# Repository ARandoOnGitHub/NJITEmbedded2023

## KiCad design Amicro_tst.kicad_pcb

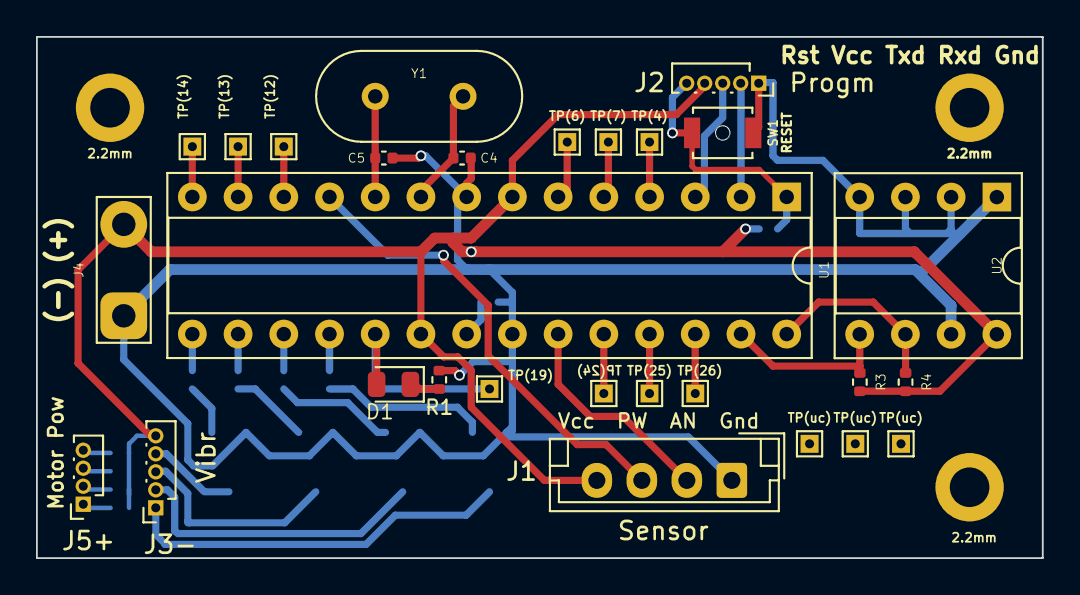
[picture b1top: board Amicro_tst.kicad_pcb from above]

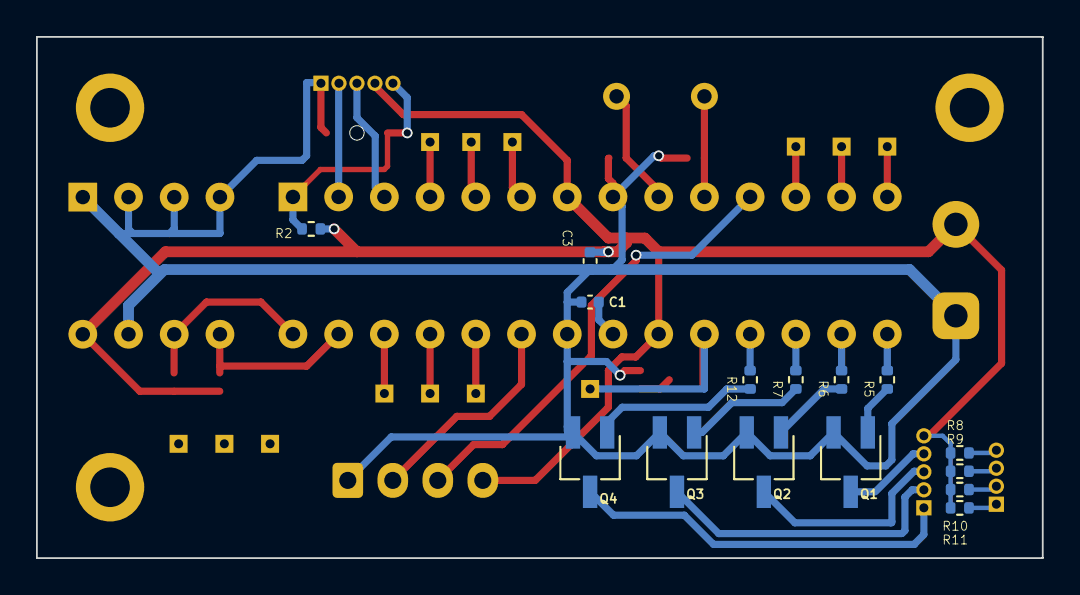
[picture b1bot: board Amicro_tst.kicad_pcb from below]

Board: 2 copper layers, 55.9 x 29.0 mm, 46 parts (15 on the bottom side), 39 nets.

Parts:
2.2mm, 2.2mm#2, 2.2mm#3: 2.2; MountingHole_2.2mm_M2_DIN965_Pad
C1, C3: .1uf; C_0402_1005Metric
C4, C5: 22pf; C_0402_1005Metric
D1: LED; LED_0805_2012Metric
J1: Sensor; JST_EH_B4B-EH-A_1x04_P2.50mm_Vertical
J2: Progm; PinSocket_1x05_P1.00mm_Vertical
J3-: Vibr; PinSocket_1x05_P1.00mm_Vertical
J4: Pow; TestPoint_2Pads_Pitch5.08mm_Drill1.3mm
J5+: Motor Pow; PinSocket_1x04_P1.00mm_Vertical
Q1, Q2, Q3, Q4: Q_NPN_BEC; SC-59_Handsoldering
R1, R5, R6, R7, R12: 1k; R_0402_1005Metric
R2: 10k; R_0402_1005Metric
R3, R4: 4.7k; R_0402_1005Metric
R8, R9, R10, R11: 33; R_0402_1005Metric
SW1: RESET; SW_SPST_B3U-1000P-B
TP(4), TP(6), TP(7), TP(12), TP(13), TP(14), TP(19), TP(24), TP(25), TP(26): TP; TestPoint_THTPad_1.0x1.0mm_Drill0.5mm
TP(uc): TP; TestPoint_THTPad_1.0x1.0mm_Drill0.5mm
TP(uc)#2, TP(uc)#3: TP; TestPoint_THTPad_1.0x1.0mm_Drill0.5mm
U1: ATmega328-P; DIP-28_W7.62mm_Socket
U2: 24LC512; DIP-8_W7.62mm_Socket
Y1: Crystal; Crystal_HC49-4H_Vertical

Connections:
AN: J1.2, U1.23 (PC0)
GND: C1.2, C3.2, C4.2, C5.2, J1.1, J2.1, J4.1, Q1.2 (E), Q2.2 (E), Q3.2 (E), Q4.2 (E), R1.1, SW1.2, U1.8 (GND), U1.22 (GND), U2.1 (A0), U2.2 (A1), U2.3 (A2), U2.4 (GND), U2.7 (WP)
M0: J3-.4, Q1.3 (C)
M1: J3-.3, Q2.3 (C)
M2: J3-.2, Q3.3 (C)
M3: J3-.1, Q4.3 (C)
Mt0+: J5+.4, R8.1
Mt1+: J5+.3, R9.1
Mt2+: J5+.2, R10.1
Mt3+: J5+.1, R11.1
unnamed: C1.1, U1.21 (AREF)
unnamed: C4.1, U1.9 (XTAL1/PB6), Y1.2
unnamed: C5.1, U1.10 (XTAL2/PB7), Y1.1
unnamed: D1.1 (K), R1.2
unnamed: D1.2 (A), TP(19).1, U1.19 (PB5)
unnamed: Q1.1 (B), R5.2
unnamed: Q2.1 (B), R6.2
unnamed: Q3.1 (B), R7.2
unnamed: Q4.1 (B), R12.2
unnamed: TP(4).1, U1.4 (PD2)
unnamed: TP(6).1, U1.6 (PD4)
unnamed: TP(7).1, U1.5 (PD3)
unnamed: TP(12).1, U1.12 (PD6)
unnamed: TP(13).1, U1.13 (PD7)
unnamed: TP(14).1, U1.14 (PB0)
unnamed: TP(24).1, U1.24 (PC1)
unnamed: TP(25).1, U1.25 (PC2)
unnamed: TP(26).1, U1.26 (PC3)
PW: J1.3, U1.11 (PD5)
PWM0: R5.1, U1.15 (PB1)
PWM1: R6.1, U1.16 (PB2)
PWM2: R7.1, U1.17 (PB3)
PWM3: R12.1, U1.18 (PB4)
RESET: J2.5, R2.2, SW1.1, U1.1 (~RESET/PC6)
RXD: J2.2, U1.2 (PD0)
SCL: R4.1, U1.28 (PC5), U2.6 (SCL)
SDA: R3.1, U1.27 (PC4), U2.5 (SDA)
TXD: J2.3, U1.3 (PD1)
VCC: C3.1, J1.4, J2.4, J3-.5, J4.2, R2.1, R3.2, R4.2, R8.2, R9.2, R10.2, R11.2, U1.7 (VCC), U1.20 (AVCC), U2.8 (VCC)

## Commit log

2023-02-03 initial files
2023-02-03 Removed Stuff
    removed unnecicarty stuff
2023-02-03 redid lost work/testpoints
    Redid lost work that didnt save, still need to find footprints for transistors
2023-02-10 transistor footprints
2023-02-13 Changed Footprints & Board Size
2023-02-14 Routing & Layout
    did some routing and changed layout
2023-02-15 Added ouline and lables
2023-02-16 Hole Alignment And Added tstpnt
2023-02-16 Added Cad files
2023-02-17 Motor schem Wrong, need redo
    old gerber files available, messed up on motor schematic, fixed schematic, need to rewire and fix board
2023-02-20 changed board/schem issue and Gerber/cad
2023-02-24 cad iges
2023-03-24 Updated Gerbers
2023-03-24 pcb update
2024-04-01 files
    gitignore stuff
